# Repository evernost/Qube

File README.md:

# Qube
LED Rubik's Cube.

Parts list
-
| Part        | Ref          | Order code       |
|-------------|--------------|------------------|
| µC          | STM32G431KB  | Farnell: 3132405 |
| LED driver  | PCA9955B     | Farnell: 2759859 |
| 3.3V LDO    | LD1117S33CTR | Farnell: 1467779 |
| Push button | KSG222GLFS   | Farnell: 2845714 |

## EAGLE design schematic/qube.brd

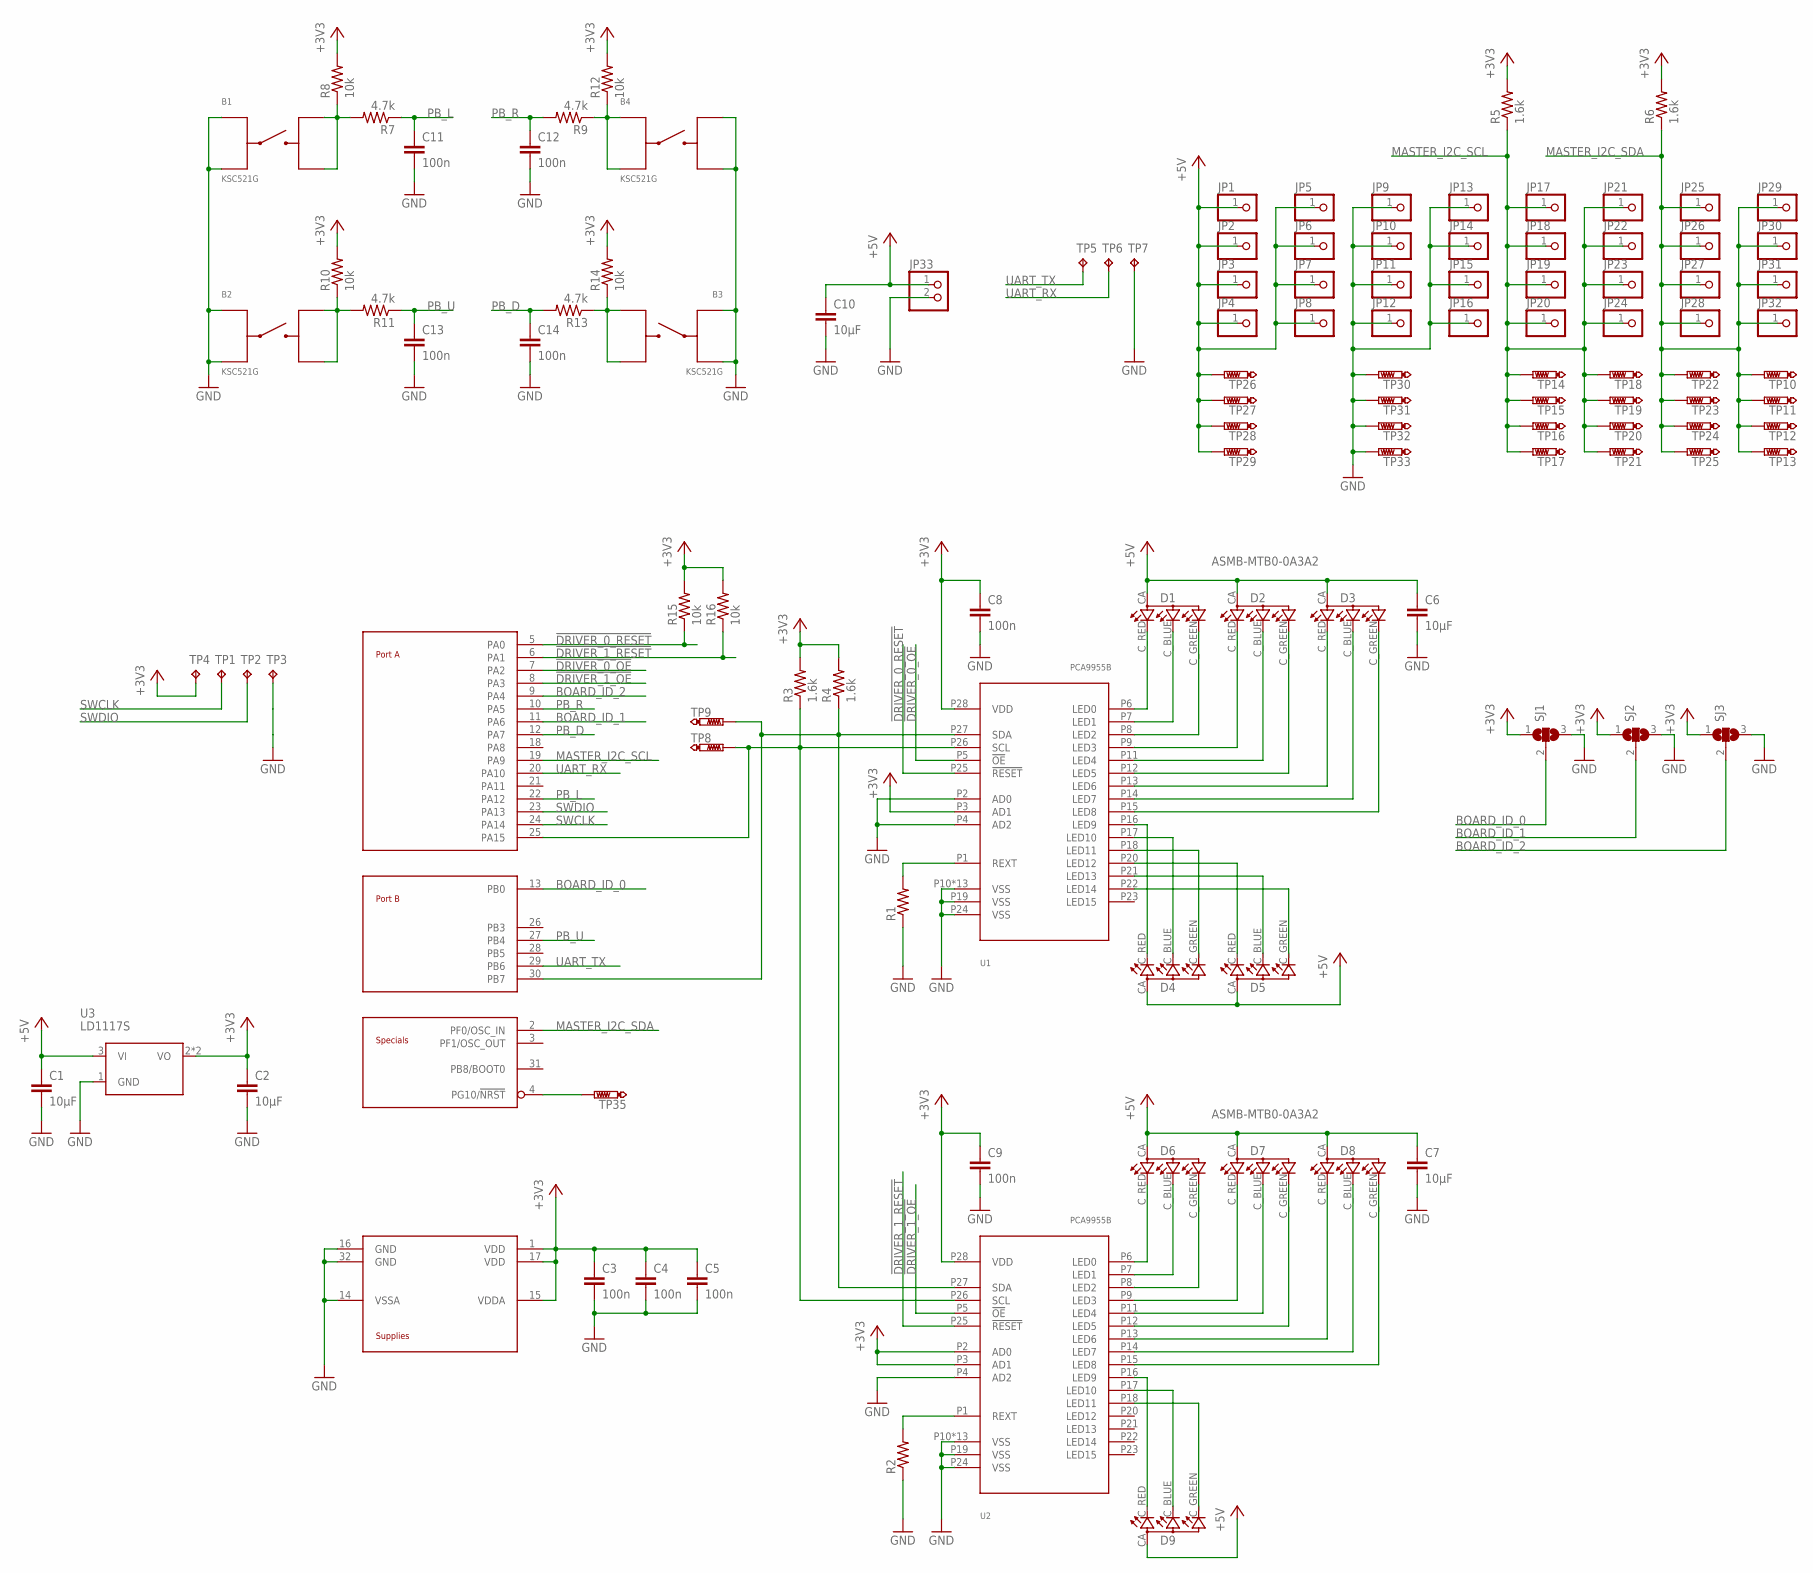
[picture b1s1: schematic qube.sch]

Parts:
B1, B2, B3, B4: KSC521G
C1, C2, C6, C7, C10: 10µF; C0805
C3, C4, C5, C8, C9, C11, C12, C13, C14: 100n; C0805
D1, D2, D3, D4, D5, D6, D7, D8, D9: ASMB-MTB0-0A3A2; PLCC-4
JP1, JP2, JP3, JP4, JP5, JP6, JP7, JP8, JP9, JP10, JP11, JP12, JP13, JP14, JP15, JP16, JP17, JP18, JP19, JP20, JP21, JP22, JP23, JP24, JP25, JP26, JP27, JP28, JP29, JP30, JP31, JP32: PINHD-1X1; 1X01
JP33: PINHD-1X2/90; 1X02/90
R1, R2: R-US_R0805; R0805
R3, R4, R5, R6: 1.6k; R0805
R7, R9, R11, R13: 4.7k; R0805
R8, R10, R12, R14, R15, R16: 10k; R0805
SJ1, SJ2, SJ3: SJ2W; SJ_2
TP1, TP2, TP3, TP4, TP5, TP6, TP7: TPTP18R; TP18R
TP8, TP9, TP10, TP11, TP12, TP13, TP14, TP15, TP16, TP17, TP18, TP19, TP20, TP21, TP22, TP23, TP24, TP25, TP26, TP27, TP28, TP29, TP30, TP31, TP32, TP33: PTR1TP15SQ; TP15SQ
TP35: PTR1TP10R; TP10R
U1, U2: PCA9955B; HTSSOP28
U3: LD1117S; SOT223
U$1: STM32G431KB; LQFP32

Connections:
!DRIVER_0_OE: U1.P5 (!OE), U$1.7 (PA2)
!DRIVER_0_RESET: R15.1, U1.P25 (!RESET), U$1.5 (PA0)
!DRIVER_1_OE: U2.P5 (!OE), U$1.8 (PA3)
!DRIVER_1_RESET: R16.1, U2.P25 (!RESET), U$1.6 (PA1)
+3V3: C2.1, C3.1, C4.1, C5.1, C8.1, C9.1, R3.2, R4.2, R5.2, R6.2, R8.2, R10.2, R12.2, R14.2, R15.2, R16.2, SJ1.1, SJ2.1, SJ3.1, TP4.TP, U1.P3 (AD1), U1.P28 (VDD), U2.P2 (AD0), U2.P3 (AD1), U2.P28 (VDD), U3.2 (VO), U3.4 (VO), U$1.1 (VDD), U$1.15 (VDDA), U$1.17 (VDD)
+5V: C1.1, C6.1, C7.1, C10.1, D1.CA (A2), D2.CA (A2), D3.CA (A2), D4.CA (A2), D5.CA (A2), D6.CA (A2), D7.CA (A2), D8.CA (A2), D9.CA (A2), JP1.1, JP2.1, JP3.1, JP4.1, JP5.1, JP6.1, JP7.1, JP8.1, JP33.1, TP26.TP, TP27.TP, TP28.TP, TP29.TP, U3.3 (VI)
BOARD_ID_0: SJ1.2, U$1.13 (PB0)
BOARD_ID_1: SJ2.2, U$1.11 (PA6)
BOARD_ID_2: SJ3.2, U$1.9 (PA4)
GND: B1.3, B1.4, B2.3, B2.4, B3.3, B3.4, B4.1, B4.2, C1.2, C2.2, C3.2, C4.2, C5.2, C6.2, C7.2, C8.2, C9.2, C10.2, C11.2, C12.2, C13.2, C14.2, JP9.1, JP10.1, JP11.1, JP12.1, JP13.1, JP14.1, JP15.1, JP16.1, JP33.2, R1.1, R2.1, SJ1.3, SJ2.3, SJ3.3, TP3.TP, TP7.TP, TP30.TP, TP31.TP, TP32.TP, TP33.TP, U1.P2 (AD0), U1.P4 (AD2), U1.P10 (VSS), U1.P19 (VSS), U1.P24 (VSS), U1.PWR_PAD1 (VSS), U1.PWR_PAD2 (VSS), U1.PWR_PAD3 (VSS), U1.PWR_PAD4 (VSS), U1.PWR_PAD5 (VSS), U1.PWR_PAD6 (VSS), U1.PWR_PAD7 (VSS), U1.PWR_PAD8 (VSS), U1.PWR_PAD9 (VSS), U1.PWR_PAD10 (VSS), U1.PWR_PAD11 (VSS), U1.PWR_PAD12 (VSS), U2.P4 (AD2), U2.P10 (VSS), U2.P19 (VSS), U2.P24 (VSS), U2.PWR_PAD1 (VSS), U2.PWR_PAD2 (VSS), U2.PWR_PAD3 (VSS), U2.PWR_PAD4 (VSS), U2.PWR_PAD5 (VSS), U2.PWR_PAD6 (VSS), U2.PWR_PAD7 (VSS), U2.PWR_PAD8 (VSS), U2.PWR_PAD9 (VSS), U2.PWR_PAD10 (VSS), U2.PWR_PAD11 (VSS), U2.PWR_PAD12 (VSS), U3.1 (GND), U$1.14 (VSSA), U$1.16 (GND), U$1.32 (GND)
MASTER_I2C_SCL: JP17.1, JP18.1, JP19.1, JP20.1, JP21.1, JP22.1, JP23.1, JP24.1, R5.1, TP14.TP, TP15.TP, TP16.TP, TP17.TP, TP18.TP, TP19.TP, TP20.TP, TP21.TP, U$1.19 (PA9)
MASTER_I2C_SDA: JP25.1, JP26.1, JP27.1, JP28.1, JP29.1, JP30.1, JP31.1, JP32.1, R6.1, TP10.TP, TP11.TP, TP12.TP, TP13.TP, TP22.TP, TP23.TP, TP24.TP, TP25.TP, U$1.2 (PF0/OSC_IN)
unnamed: R1.2, U1.P1 (REXT)
unnamed: R2.2, U2.P1 (REXT)
unnamed: D1.C_RED (CRED), U1.P6 (LED0)
unnamed: D1.C_BLUE (CBLUE), U1.P7 (LED1)
unnamed: D1.C_GREEN (CGREEN), U1.P8 (LED2)
unnamed: D2.C_RED (CRED), U1.P9 (LED3)
unnamed: D2.C_BLUE (CBLUE), U1.P11 (LED4)
unnamed: D2.C_GREEN (CGREEN), U1.P12 (LED5)
unnamed: D3.C_RED (CRED), U1.P13 (LED6)
unnamed: D3.C_BLUE (CBLUE), U1.P14 (LED7)
unnamed: D3.C_GREEN (CGREEN), U1.P15 (LED8)
unnamed: D4.C_RED (CRED), U1.P16 (LED9)
unnamed: D4.C_BLUE (CBLUE), U1.P17 (LED10)
unnamed: D4.C_GREEN (CGREEN), U1.P18 (LED11)
unnamed: D5.C_RED (CRED), U1.P20 (LED12)
unnamed: D5.C_BLUE (CBLUE), U1.P21 (LED13)
unnamed: D5.C_GREEN (CGREEN), U1.P22 (LED14)
unnamed: D6.C_RED (CRED), U2.P6 (LED0)
unnamed: D6.C_BLUE (CBLUE), U2.P7 (LED1)
unnamed: D6.C_GREEN (CGREEN), U2.P8 (LED2)
unnamed: D7.C_RED (CRED), U2.P9 (LED3)
unnamed: D7.C_BLUE (CBLUE), U2.P11 (LED4)
unnamed: D7.C_GREEN (CGREEN), U2.P12 (LED5)
unnamed: D8.C_RED (CRED), U2.P13 (LED6)
unnamed: D8.C_BLUE (CBLUE), U2.P14 (LED7)
unnamed: D8.C_GREEN (CGREEN), U2.P15 (LED8)
unnamed: D9.C_RED (CRED), U2.P16 (LED9)
unnamed: D9.C_BLUE (CBLUE), U2.P17 (LED10)
unnamed: D9.C_GREEN (CGREEN), U2.P18 (LED11)
unnamed: R3.1, TP8.TP, U1.P26 (SCL), U2.P26 (SCL), U$1.25 (PA15)
unnamed: R4.1, TP9.TP, U1.P27 (SDA), U2.P27 (SDA), U$1.30 (PB7)
unnamed: B1.1, B1.2, R7.2, R8.1
unnamed: B3.1, B3.2, R13.1, R14.1
unnamed: B4.3, B4.4, R9.1, R12.1
unnamed: TP35.TP, U$1.4 (PG10/!NRST)
unnamed: B2.1, B2.2, R10.1, R11.2
PB_D: C14.1, R13.2, U$1.12 (PA7)
PB_L: C11.1, R7.1, U$1.22 (PA12)
PB_R: C12.1, R9.2, U$1.10 (PA5)
PB_U: C13.1, R11.1, U$1.27 (PB4)
SWCLK: TP1.TP, U$1.24 (PA14)
SWDIO: TP2.TP, U$1.23 (PA13)
UART_RX: TP6.TP, U$1.20 (PA10)
UART_TX: TP5.TP, U$1.29 (PB6)

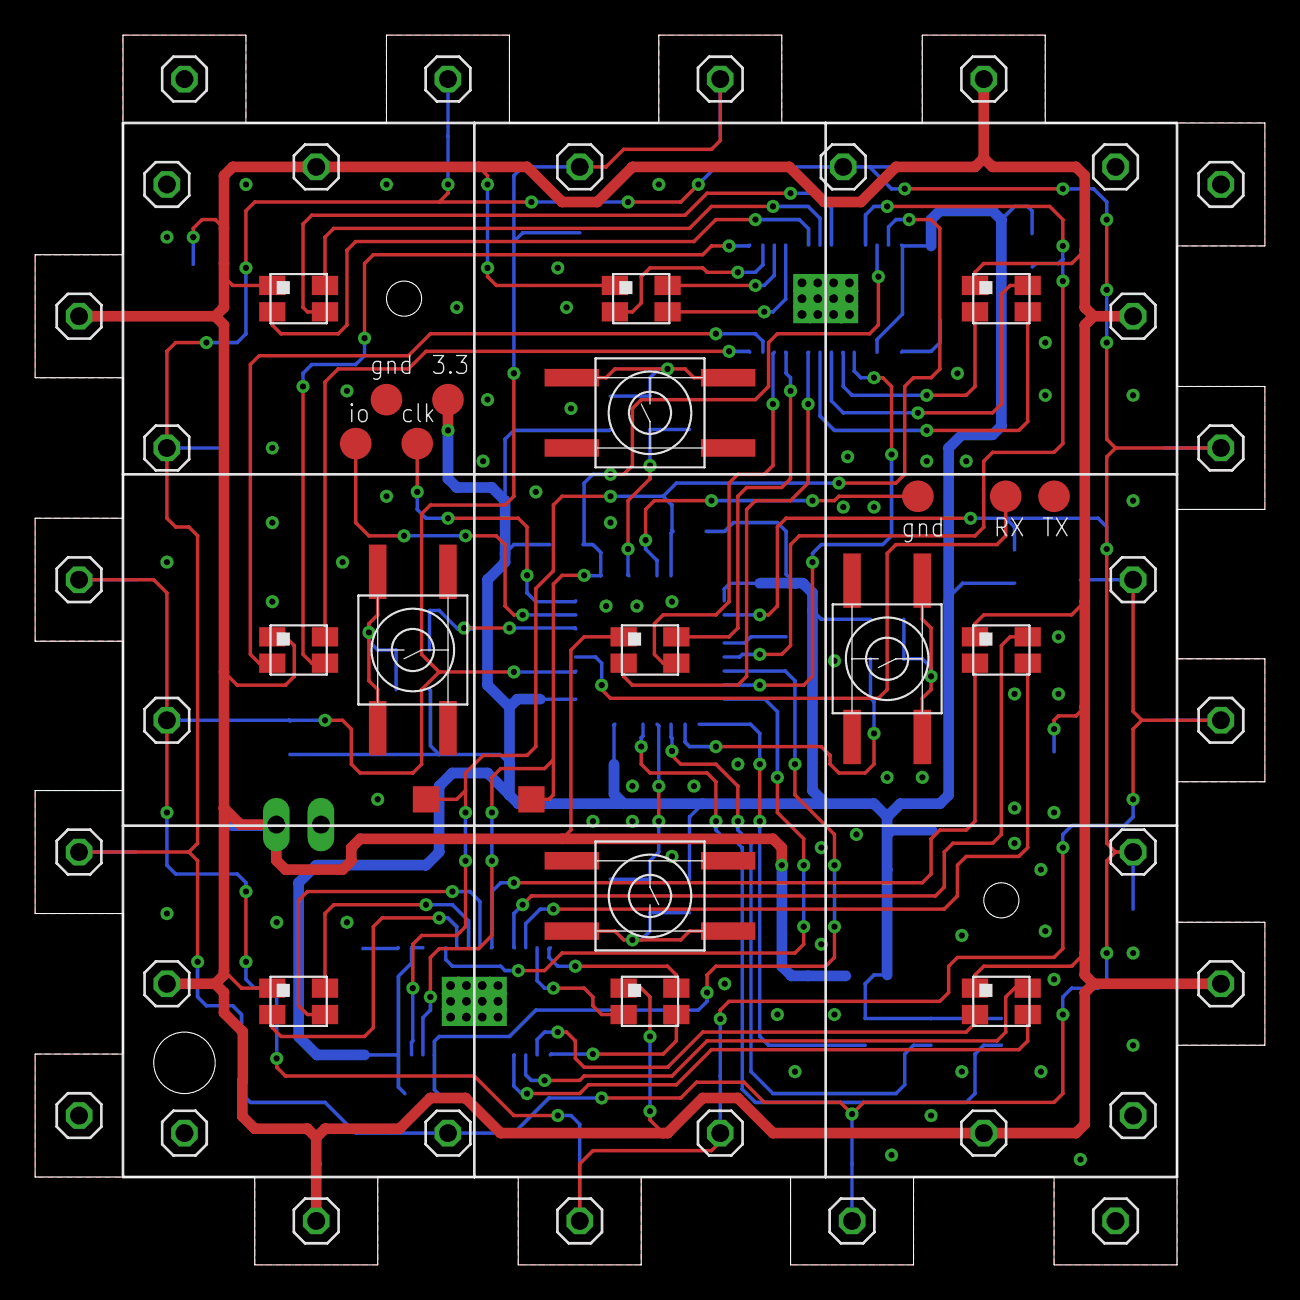
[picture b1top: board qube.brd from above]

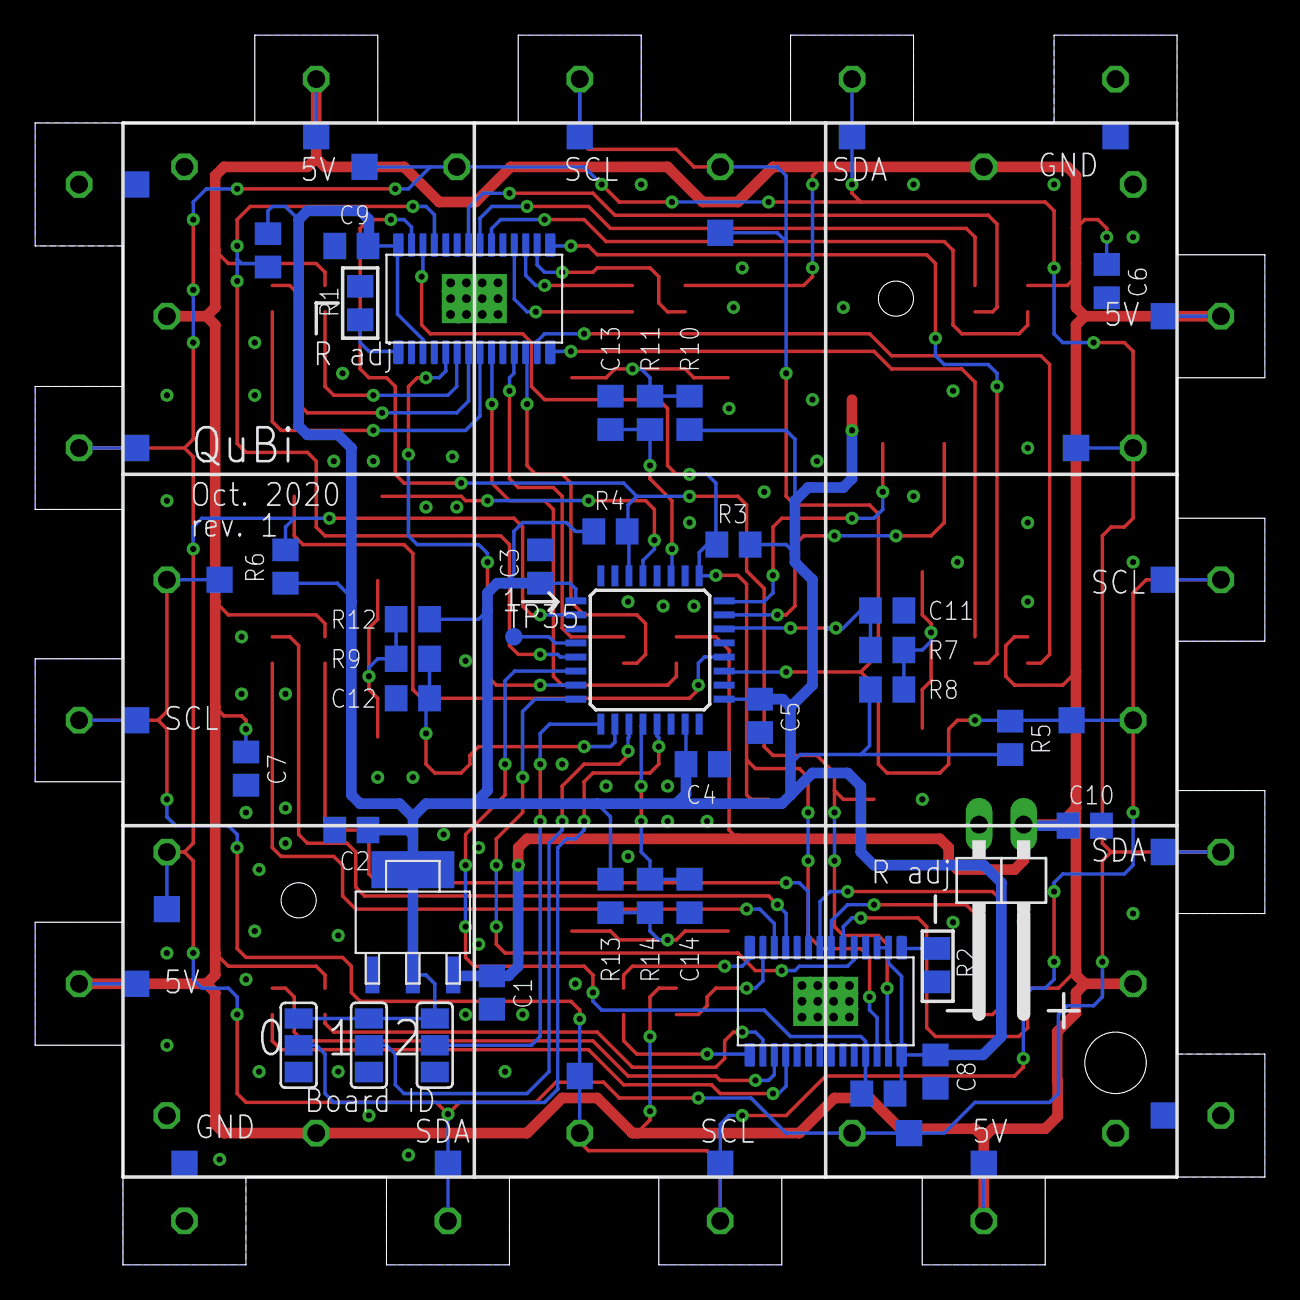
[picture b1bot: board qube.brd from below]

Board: 2 copper layers, 70.0 x 70.0 mm, 117 parts (63 on the bottom side), 56 nets.

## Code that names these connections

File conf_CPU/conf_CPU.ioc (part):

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Mcu.Name=STM32G431K(6-8-B)Tx
Mcu.Package=LQFP32
Mcu.UserName=STM32G431KBTx
PA0.GPIOParameters=GPIO_Label
PA0.GPIO_Label=DRIVER_0_RESET
PA0.Signal=GPIO_Output
PA1.GPIOParameters=GPIO_Label
PA1.GPIO_Label=DRIVER_1_RESET
PA1.Signal=GPIO_Output
PA10.Mode=Asynchronous
PA10.Signal=USART1_RX
PA12.GPIOParameters=GPIO_Label
PA12.GPIO_Label=PB_left
PA12.Signal=GPIO_Input
PA13.Mode=Serial_Wire
PA13.Signal=SYS_JTMS-SWDIO
PA14.Mode=Serial_Wire
PA14.Signal=SYS_JTCK-SWCLK
PA15.GPIOParameters=GPIO_PuPdOD,GPIO_Label,GPIO_Mode
PA15.GPIO_Label=I2C1_LED_DRV_SCL
PA15.GPIO_Mode=GPIO_MODE_AF_OD
PA15.GPIO_PuPdOD=GPIO_NOPULL
PA15.Mode=I2C
PA15.Signal=I2C1_SCL
PA2.GPIOParameters=PinState,GPIO_Label
PA2.GPIO_Label=DRIVER_0_OE
PA2.PinState=GPIO_PIN_SET
PA2.Signal=GPIO_Output
PA3.GPIOParameters=PinState,GPIO_Label
PA3.GPIO_Label=DRIVER_1_OE
PA3.PinState=GPIO_PIN_SET
PA3.Signal=GPIO_Output
PA4.GPIOParameters=GPIO_Label
PA4.GPIO_Label=BOARD_ID_0
PA4.Signal=GPIO_Input
PA5.GPIOParameters=GPIO_Label
PA5.GPIO_Label=PB_right
PA5.Signal=GPIO_Input
PA6.GPIOParameters=GPIO_Label
PA6.GPIO_Label=BOARD_ID_1
PA6.Signal=GPIO_Input
PA7.GPIOParameters=GPIO_Label
PA7.GPIO_Label=PB_down
PA7.Signal=GPIO_Input
PA9.GPIOParameters=GPIO_Label
PA9.GPIO_Label=I2C2_COMM_SCL
PA9.Mode=I2C
PA9.Signal=I2C2_SCL
PB0.GPIOParameters=GPIO_Label
PB0.GPIO_Label=BOARD_ID_2
PB0.Signal=GPIO_Input
PB4.GPIOParameters=GPIO_Label
PB4.GPIO_Label=PB_up
PB4.Signal=GPIO_Input
PB6.Mode=Asynchronous
PB6.Signal=USART1_TX
PB7.GPIOParameters=GPIO_PuPdOD,GPIO_Label,GPIO_FM7,GPIO_Mode
PB7.GPIO_FM7=SYSCFG_FASTMODEPLUS_PB7
PB7.GPIO_Label=I2C1_LED_DRV_SDA
PB7.GPIO_Mode=GPIO_MODE_AF_OD
PB7.GPIO_PuPdOD=GPIO_NOPULL
PB7.Mode=I2C
PB7.Signal=I2C1_SDA
PB8-BOOT0.Signal=GPIO_Output
PF0-OSC_IN.GPIOParameters=GPIO_Label
PF0-OSC_IN.GPIO_Label=I2C2_COMM_SDA
PF0-OSC_IN.Mode=I2C
PF0-OSC_IN.Signal=I2C2_SDA
RCC.HSE_VALUE=8000000
RCC.SYSCLKFreq_VALUE=160000000
RCC.SYSCLKSource=RCC_SYSCLKSOURCE_PLLCLK
board=custom

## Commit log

2022-06-04 First upload of the current progress state.
2022-06-25 Code re-organized, split in several .c files. First working version with basic moves shown. Core for move computation is integrated.
2022-11-01 - Deleted unused "common.h" - Code rework and cleanup - Changed for more consistent variable names
